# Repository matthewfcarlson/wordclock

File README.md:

# wordclock
a word clock for Sara, much like qlocktwo, but much much less. This repo contains the c code as well as the PCB files, renders, and other drawings that will aid you in creating your own if you so desire.

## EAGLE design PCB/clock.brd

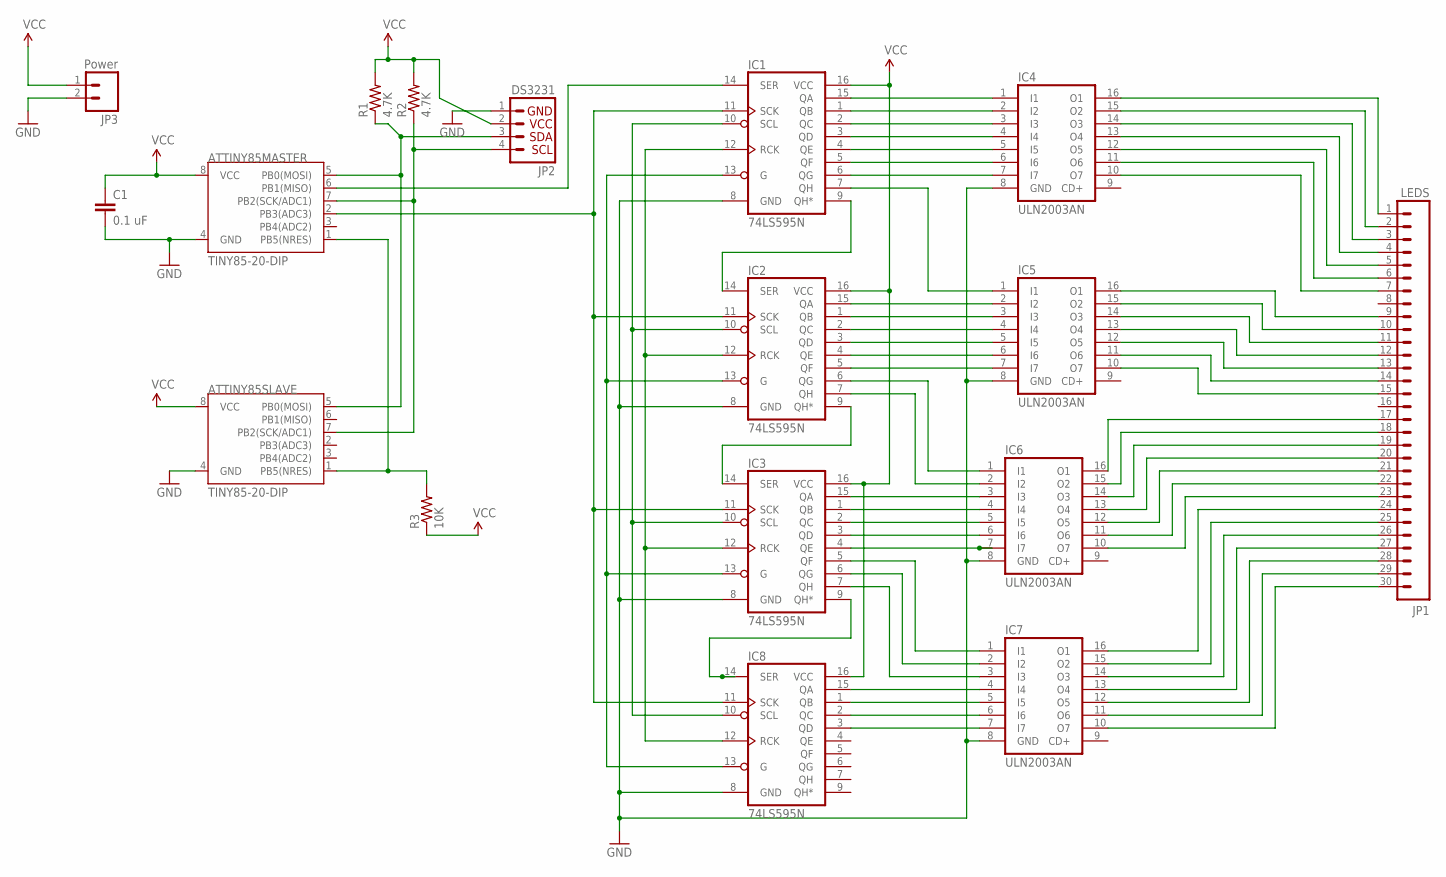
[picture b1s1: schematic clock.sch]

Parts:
ATTINY85MASTER, ATTINY85SLAVE: TINY85-20-DIP; DIP08
C1: 0.1 uF; CAP-PTH-SMALL
IC1, IC2, IC3, IC8: 74LS595N; DIL16
IC4, IC5, IC6, IC7: ULN2003AN; DIL16
JP1: LEDS; 1X30
JP2: DS3231; 1X04
JP3: Power; 1X02_LONGPADS
R1, R2: 4.7K; AXIAL-0.4
R3: 10K; AXIAL-0.4

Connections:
GND: ATTINY85MASTER.4 (GND), ATTINY85SLAVE.4 (GND), C1.2, IC1.8 (GND), IC2.8 (GND), IC3.8 (GND), IC4.8 (GND), IC5.8 (GND), IC6.8 (GND), IC7.8 (GND), IC8.8 (GND), JP2.1, JP3.2
HALF: IC4.15 (O2), JP1.2
unnamed: ATTINY85MASTER.5 (PB0(MOSI)), ATTINY85SLAVE.5 (PB0(MOSI)), JP2.3, R1.P$1 (1)
unnamed: ATTINY85MASTER.7 (PB2(SCK/ADC1)), ATTINY85SLAVE.7 (PB2(SCK/ADC1)), JP2.4, R2.P$1 (1)
unnamed: IC1.9 (QH*), IC2.14 (SER)
unnamed: IC1.13 (G), IC2.13 (G), IC3.13 (G), IC8.13 (G)
unnamed: IC2.9 (QH*), IC3.14 (SER)
unnamed: ATTINY85MASTER.1 (PB5(NRES)), ATTINY85SLAVE.1 (PB5(NRES)), R3.P$2 (2)
unnamed: IC1.15 (QA), IC4.1 (I1)
unnamed: IC1.1 (QB), IC4.2 (I2)
unnamed: IC1.2 (QC), IC4.3 (I3)
unnamed: IC1.3 (QD), IC4.4 (I4)
unnamed: IC1.4 (QE), IC4.5 (I5)
unnamed: IC1.5 (QF), IC4.6 (I6)
unnamed: IC1.6 (QG), IC4.7 (I7)
unnamed: ATTINY85MASTER.6 (PB1(MISO)), IC1.14 (SER)
unnamed: IC1.7 (QH), IC5.1 (I1)
unnamed: IC2.15 (QA), IC5.2 (I2)
unnamed: IC2.1 (QB), IC5.3 (I3)
unnamed: IC2.2 (QC), IC5.4 (I4)
unnamed: IC2.3 (QD), IC5.5 (I5)
unnamed: IC2.4 (QE), IC5.6 (I6)
unnamed: IC2.5 (QF), IC5.7 (I7)
unnamed: IC2.7 (QH), IC6.2 (I2)
unnamed: IC2.6 (QG), IC6.1 (I1)
unnamed: IC3.15 (QA), IC6.3 (I3)
unnamed: IC3.1 (QB), IC6.4 (I4)
unnamed: IC3.2 (QC), IC6.5 (I5)
unnamed: IC3.3 (QD), IC6.6 (I6)
unnamed: IC3.4 (QE), IC6.7 (I7)
unnamed: IC3.9 (QH*), IC8.14 (SER)
unnamed: IC7.4 (I4), IC8.15 (QA)
unnamed: IC7.5 (I5), IC8.1 (QB)
unnamed: IC7.6 (I6), IC8.2 (QC)
unnamed: IC7.7 (I7), IC8.3 (QD)
unnamed: IC3.5 (QF), IC7.1 (I1)
unnamed: IC3.6 (QG), IC7.2 (I2)
unnamed: IC3.7 (QH), IC7.3 (I3)
unnamed: IC1.10 (SCL), IC2.10 (SCL), IC3.10 (SCL), IC8.10 (SCL)
unnamed: IC1.12 (RCK), IC2.12 (RCK), IC3.12 (RCK), IC8.12 (RCK)
unnamed: IC4.14 (O3), JP1.3
unnamed: IC4.13 (O4), JP1.4
unnamed: IC4.12 (O5), JP1.5
unnamed: IC4.11 (O6), JP1.6
unnamed: IC4.10 (O7), JP1.7
unnamed: ATTINY85MASTER.2 (PB3(ADC3)), IC1.11 (SCK), IC2.11 (SCK), IC3.11 (SCK), IC8.11 (SCK)
unnamed: IC5.16 (O1), JP1.9
unnamed: IC5.15 (O2), JP1.10
unnamed: IC5.14 (O3), JP1.11
unnamed: IC5.13 (O4), JP1.12
unnamed: IC5.12 (O5), JP1.13
unnamed: IC5.11 (O6), JP1.14
unnamed: IC5.10 (O7), JP1.15
unnamed: IC7.16 (O1), JP1.24
unnamed: IC6.16 (O1), JP1.17
unnamed: IC6.15 (O2), JP1.18
unnamed: IC6.14 (O3), JP1.19
unnamed: IC6.13 (O4), JP1.20
unnamed: IC6.12 (O5), JP1.21
unnamed: IC6.11 (O6), JP1.22
unnamed: IC6.10 (O7), JP1.23
unnamed: IC7.15 (O2), JP1.25
unnamed: IC7.14 (O3), JP1.26
unnamed: IC7.13 (O4), JP1.27
unnamed: IC7.12 (O5), JP1.28
unnamed: IC7.11 (O6), JP1.29
unnamed: IC7.10 (O7), JP1.30
TEN: IC4.16 (O1), JP1.1
VCC: ATTINY85MASTER.8 (VCC), ATTINY85SLAVE.8 (VCC), C1.1, IC1.16 (VCC), IC2.16 (VCC), IC3.16 (VCC), IC8.16 (VCC), JP2.2, JP3.1, R1.P$2 (2), R2.P$2 (2), R3.P$1 (1)

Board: 2 copper layers, 17 parts (0 on the bottom side), 69 nets, no tracks yet.

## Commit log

2015-06-29 Added code and readme
2015-07-07 added the PCB file
2015-07-07 Updated Schematic
2015-07-07 Added a render
2015-07-07 Added the clock face vector
2015-07-08 Updated the schematic for better readability
2015-07-10 Some possible layouts for the clock
2015-07-10 Added a new possible layout
2015-07-11 Updated the board with the darlington arrays and whatnot
2015-07-11 Added the autorouted layout
2015-07-13 Made the clock face bold and added a bit of spacing
2015-07-17 Added her symbol
2015-07-17 Render of her symbol (laser cut)
2015-07-20 Added a fun thing to laser cut for later
2015-07-22 added solid symbol for etching
2015-08-15 added the code to determine the configuration bits for the LEDS

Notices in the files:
parts and their libraries:
SparkFun-DigitalIC: Licensing: Creative Commons ShareAlike 4.0 International - https://creativecommons.org/licenses/by-sa/4.0
